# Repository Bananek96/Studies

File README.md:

# Issues performed during studies
- Python codes: [python](./python)
- Cpp codes: [cpp](./cpp)
- Matlab programms & algorithms: [Matlab](./Matlab)
- Linux/Unix codes & programs based on Linux/Unix systems: [Linux_&_Unix](./Linux_&_Unix)
- Construction of electronics devices project using LTSpice and KiCad- 'Pipek dręczyciel': [Construction of electronic devices](./Construction_of_electronic_devices)
- LabView programms: [LabView](./LabView)
- Database & SQL: [database](./database)

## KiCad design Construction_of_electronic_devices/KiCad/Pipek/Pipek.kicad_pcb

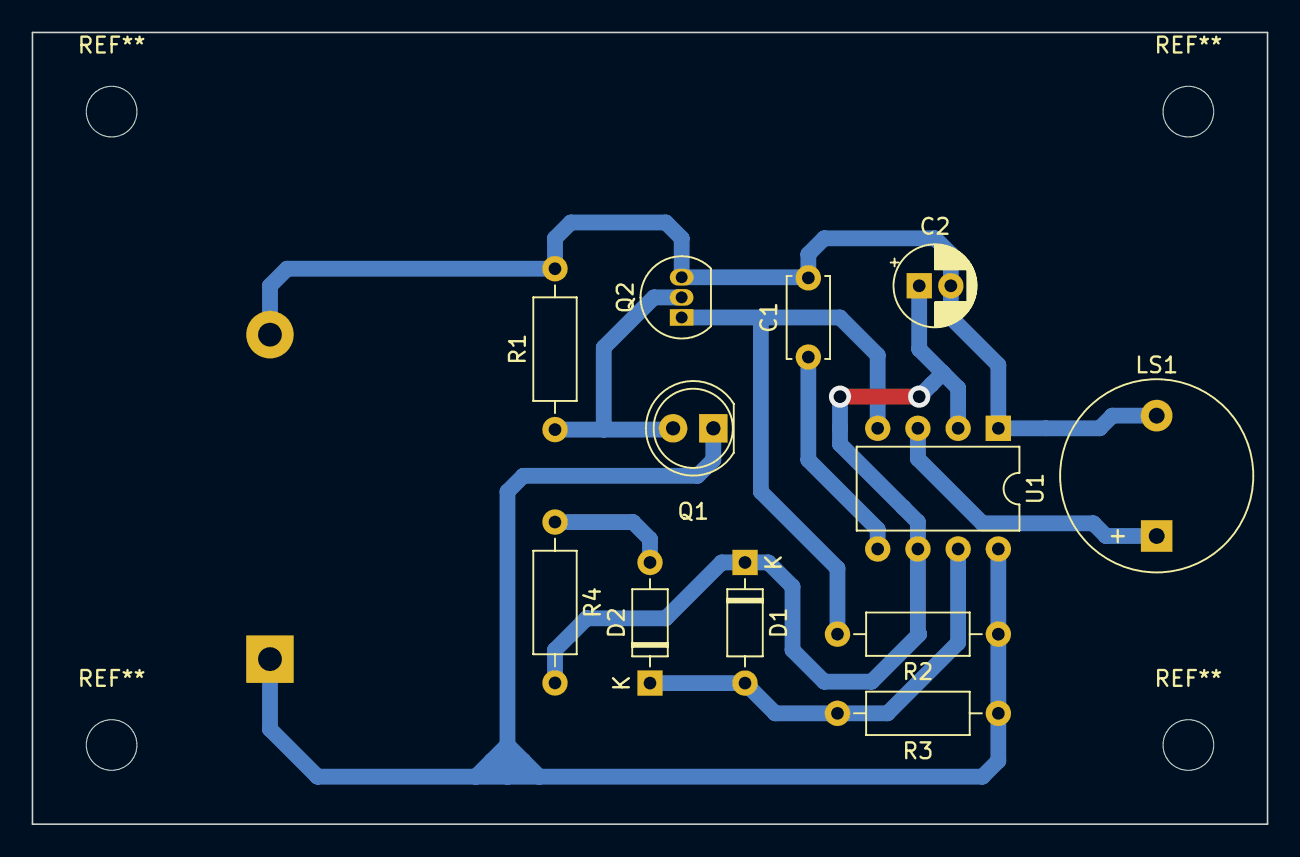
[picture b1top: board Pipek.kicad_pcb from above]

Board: 2 copper layers, 78.0 x 50.0 mm, 13 parts (1 on the bottom side), 9 nets.

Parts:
BT1: 3...6V; BatteryHolder_Keystone_106_1x20mm
C1: 10n; C_Disc_D5.0mm_W2.5mm_P5.00mm
C2: 10u; CP_Radial_D5.0mm_P2.00mm
D1, D2: 1N4148; D_DO-35_SOD27_P7.62mm_Horizontal
LS1: Piezo; Buzzer_12x9.5RM7.6
Q1: BPW40; LED_D5.0mm_Clear
Q2: BC548; TO-92_Inline
R1, R2: 100k; R_Axial_DIN0207_L6.3mm_D2.5mm_P10.16mm_Horizontal
R3: 1k; R_Axial_DIN0207_L6.3mm_D2.5mm_P10.16mm_Horizontal
R4: 1M; R_Axial_DIN0207_L6.3mm_D2.5mm_P10.16mm_Horizontal
U1: NE555P; DIP-8_W7.62mm

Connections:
GND: BT1.2 (-), C1.2, C2.2, LS1.2, Q2.3 (E), R1.2, U1.1 (GND)
unnamed: BT1.1 (+), Q1.1 (C), R2.1, R3.1, U1.8 (VCC)
unnamed: C1.1, U1.5 (CV)
unnamed: C2.1, D1.1 (K), R4.2, U1.2 (TR), U1.6 (THR)
unnamed: D1.2 (A), D2.1 (K), R3.2, U1.7 (DIS)
unnamed: D2.2 (A), R4.1
unnamed: LS1.1, U1.3 (Q)
unnamed: Q1.2 (E), Q2.2 (B), R1.1
unnamed: Q2.1 (C), R2.2, U1.4 (R)

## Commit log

2022-09-23 Inicjalizacja
2022-11-07 katalogi
2023-01-09 Codes update
2023-01-09 Image Analysis
2023-02-19 Basic codes
2023-03-08 Folder update
2023-03-16 New algorithms
2023-03-16 Object excercises
2023-03-16 Codes update from 1st & 2nd year
2023-03-16 high school course
2023-03-16 LabView_update
2023-03-23 Studies codes update
2023-03-23 Unix & Linux
2023-03-24 Linux update
    change folders name
2023-03-24 Folder name changes
2025-05-20 PROJEKTY
